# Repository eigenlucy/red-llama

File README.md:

# red-llama

Wooohooo a new package!

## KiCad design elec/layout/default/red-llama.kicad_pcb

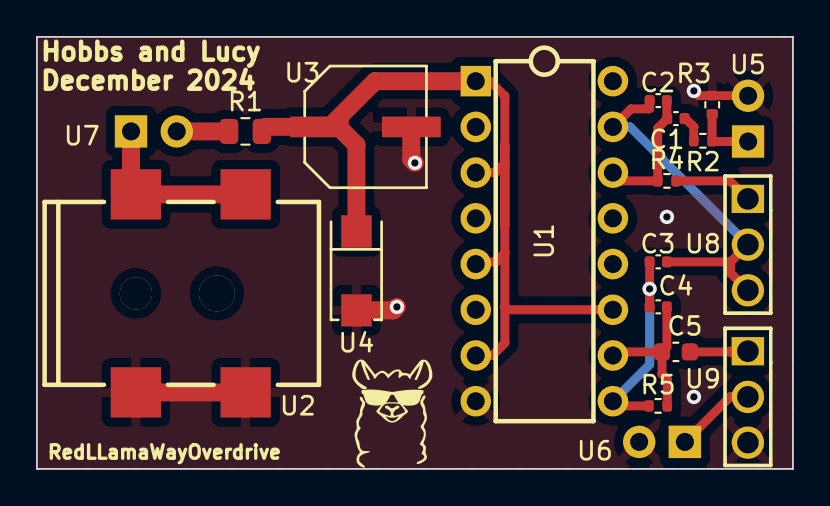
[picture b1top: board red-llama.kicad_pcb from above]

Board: 2 copper layers, 42.0 x 24.0 mm, 19 parts (0 on the bottom side), 14 nets.

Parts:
C1: 50V 68nF X7R ±10% 0402 Multilayer Ceramic Capacit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; C0402
C2: 50V 47pF C0G ±5% 0402 Multilayer Ceramic Capacito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; C0402
C3: 16V 33nF X7R ±10% 0402 Multilayer Ceramic Capacit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; C0402
C4: 50V 100pF C0G ±5% 0402 Multilayer Ceramic Capacit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; C0402
C5: 10V 10uF X5R ±10% 0603 Multilayer Ceramic Capacit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; C0603
R1: 125mW Thick Film Resistors 150V ±100ppm/℃ ±1% 1kΩ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; R0805
R2, R4: 62.5mW Thick Film Resistors 50V ±100ppm/℃ ±1% 100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; R0402
R3, R5: 62.5mW Thick Film Resistors 50V ±100ppm/℃ ±1% 1MΩ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; R0402
U1: ?; PDIP-16_L19.7-W6.6-P2.54-LS7.6-BL
U2: ?; DC-IN-TH_DC-005-5A-2.0-SMT
U3: ?; CAP-SMD_BD6.3-L6.6-W6.6-LS7.2-R-RD
U4: ?; SMA_L4.5-W2.7-LS5.1-RD
U5, U6, U7: ?; HDR-TH_2P-P2.54-V-M-1
U8, U9: ?; HDR-TH_3P-P2.54-V-M-1

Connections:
C6-gnd: C5.2, U9.1
R2-vcc: C1.1, R2.2
d: C3.2, C4.1, R5.1, U1.9
dc_jack-vcc: U2.1, U7.1
f: C1.2, C2.1, R4.1, U1.14
gnd: R3.2, U1.8, U2.2, U2.3, U3.2, U4.2, U5.2, U6.2, U9.3
input: R2.1, R3.1, U5.1
j_equal_d_hash: C4.2, C5.1, R5.2, U1.10
l_equal_f_hash: C2.2, C3.1, U1.15, U8.2, U8.3
nc: U1.13, U1.16
output: U6.1, U9.2
p1: R1.1, U7.2
p2: R4.2, U8.1
vcc: R1.2, U1.1, U1.3, U1.5, U1.7, U1.11, U3.1, U4.1

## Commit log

2024-12-14 Configure project
2024-12-16 edits
2024-12-18 fini
